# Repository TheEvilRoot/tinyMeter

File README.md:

# tinyMeter

Current/voltage meter board for:
- USB-C passthrough with PD support
- USB-C - USB-A 5V rail 
- DC-Jack passthrough

ESP32-S3 MCU is powered from separate master USB-C port with USB communication enabled. MCU is communicating with INA3221 IC via I2C. Separate I2C lines are connected to SSD1306 display connector (GND, 3V3, SCL, SDA). MCU also connected to 5 user buttons for user interaction and 3 LEDs.

## PCB

Board is implemented as 4-layer PCB with [Signal/GND - GND - 3V3 - Signal/GND] stackup (theoretically can be shrinked to 2 layers).

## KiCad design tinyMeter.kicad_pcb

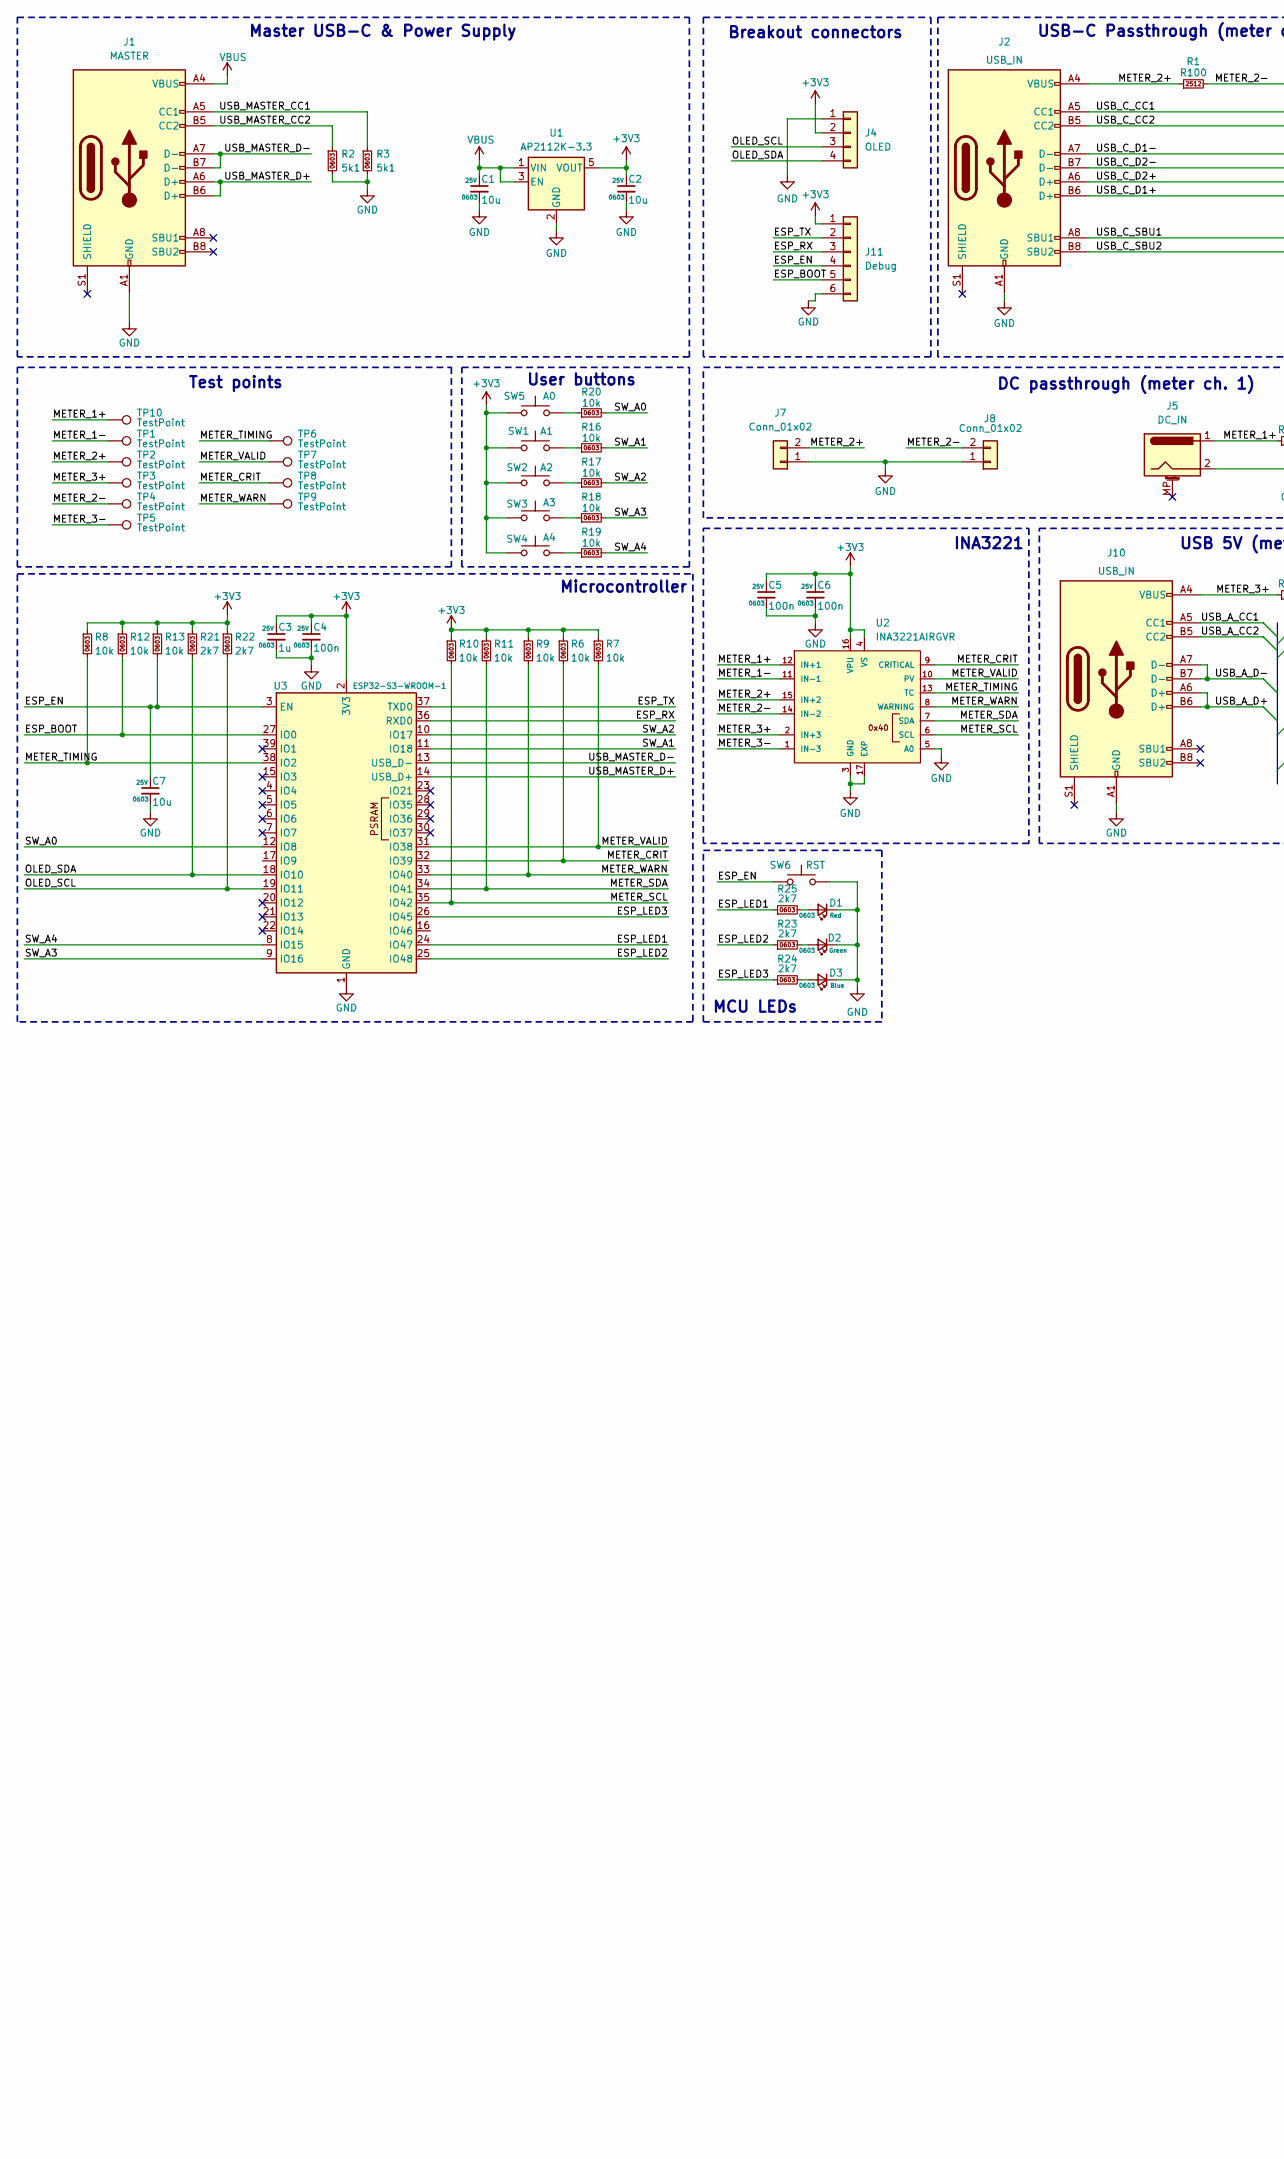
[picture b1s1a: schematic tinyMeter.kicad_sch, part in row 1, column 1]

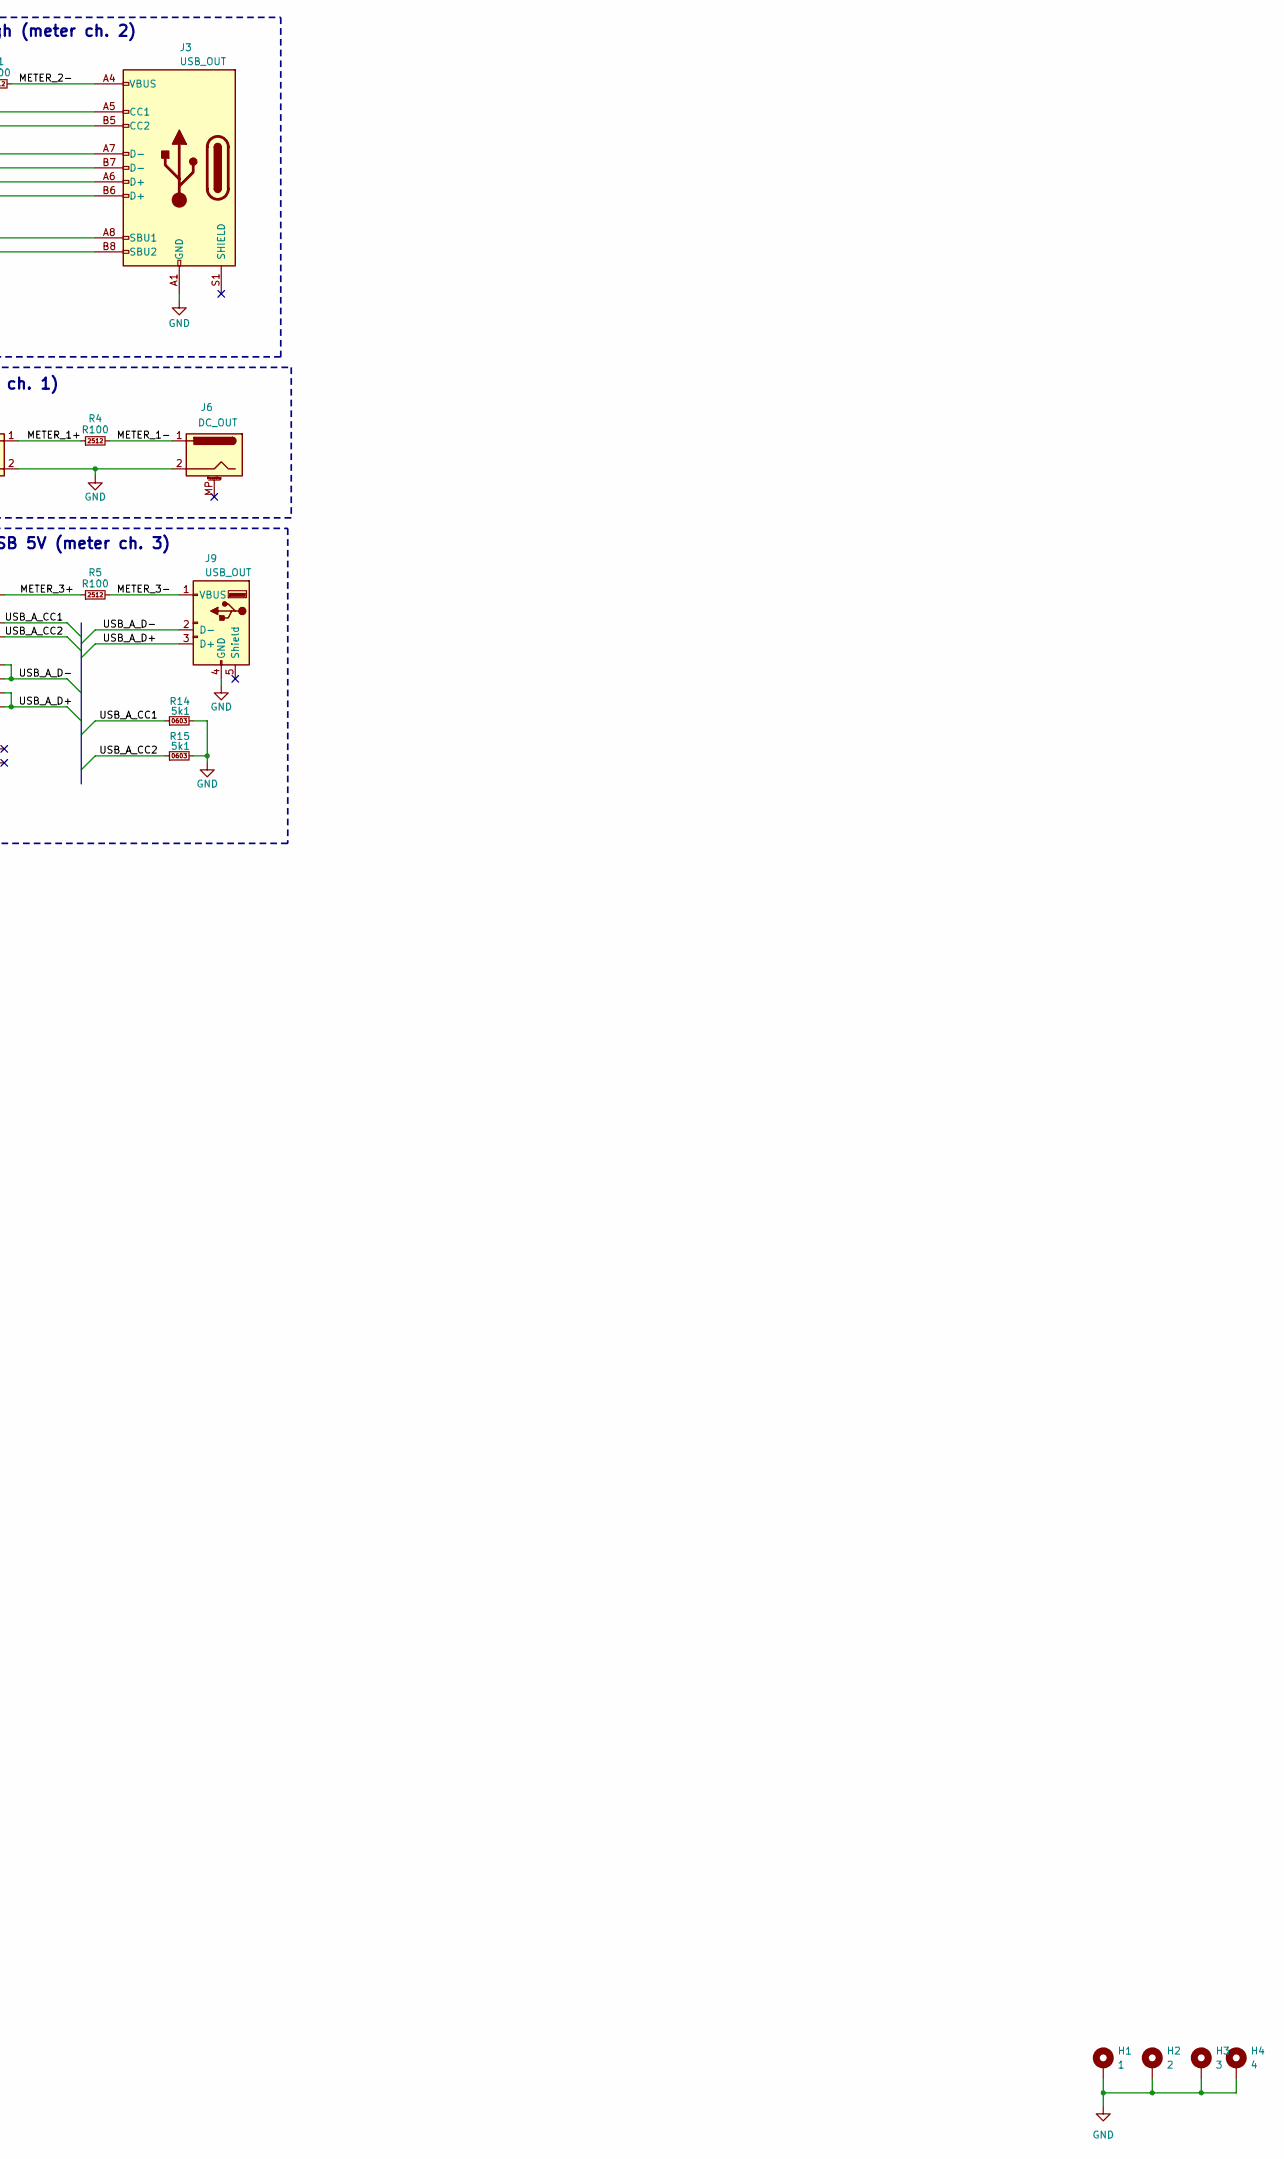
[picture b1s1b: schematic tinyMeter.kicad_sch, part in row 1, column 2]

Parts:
C1, C2, C7: 10u; C_0603_1608Metric; Rating 25V
C3: 1u; C_0603_1608Metric; Rating 25V
C4, C5, C6: 100n; C_0603_1608Metric; Rating 25V
D1: Red; LED_0603_1608Metric
D2: Green; LED_0603_1608Metric
D3: Blue; LED_0603_1608Metric
H1: 1; MountingHole_2.7mm_M2.5_DIN965_Pad
H2: 2; MountingHole_2.7mm_M2.5_DIN965_Pad
H3: 3; MountingHole_2.7mm_M2.5_DIN965_Pad
H4: 4; MountingHole_2.7mm_M2.5_DIN965_Pad
J1: MASTER; USB_C_Receptacle_HRO_TYPE-C-31-M-12
J2, J10: USB_IN; USB_C_Receptacle_HRO_TYPE-C-31-M-12
J3: USB_OUT; USB_C_Receptacle_HRO_TYPE-C-31-M-12
J4: OLED; PinSocket_1x04_P2.54mm_Vertical
J5: DC_IN; BarrelJack_Horizontal
J6: DC_OUT; BarrelJack_Horizontal
J7, J8: Conn_01x02; PinHeader_1x02_P2.54mm_Vertical
J9: USB_OUT; TE_292303-1
J11: Debug; PinHeader_1x06_P1.27mm_Vertical
R1, R4, R5: R100; R_2512_6332Metric
R2, R3, R14, R15: 5k1; R_0603_1608Metric
R6, R7, R8, R9, R10, R11, R12, R13, R16, R17, R18, R19, R20: 10k; R_0603_1608Metric
R21, R22, R23, R24, R25: 2k7; R_0603_1608Metric
SW1: A1; KLS7-TS3401
SW2: A2; KLS7-TS3401
SW3: A3; KLS7-TS3401
SW4: A4; KLS7-TS3401
SW5: A0; KLS7-TS3401
SW6: RST; KLS7-TS3401
TP1, TP2, TP3, TP4, TP5, TP6, TP7, TP8, TP9, TP10: TestPoint; TestPoint_Pad_D1.0mm
U1: AP2112K-3.3; SOT-23-5
U2: INA3221AIRGVR; QFN65P400X400X100-17N
U3: ESP32-S3-WROOM-1

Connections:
+3V3: C2.1, C3.1, C4.1, C5.1, C6.1, J4.2, J11.1, R6.1, R7.1, R8.1, R9.1, R10.1, R11.1, R12.1, R13.1, R21.1, R22.1, SW1.1, SW2.1, SW3.1, SW4.1, SW5.1, U1.5 (VOUT), U2.4 (VS), U2.16 (VPU), U3.2 (3V3)
/ESP_BOOT: J11.5, R12.2, U3.27 (IO0)
/ESP_EN: C7.1, J11.4, R13.2, SW6.1, U3.3 (EN)
/ESP_LED1: R25.1, U3.24 (IO47)
/ESP_LED2: R23.1, U3.25 (IO48)
/ESP_LED3: R24.1, U3.26 (IO45)
/ESP_RX: J11.3, U3.36 (RXD0)
/ESP_TX: J11.2, U3.37 (TXD0)
/METER_1+: J5.1, R4.1, TP10.1, U2.12 (IN+1)
/METER_1-: J6.1, R4.2, TP1.1, U2.11 (IN-1)
/METER_2+: J2.A4 (VBUS), J2.A9 (VBUS), J2.B4 (VBUS), J2.B9 (VBUS), J7.2, R1.1, TP2.1, U2.15 (IN+2)
/METER_2-: J3.A4 (VBUS), J3.A9 (VBUS), J3.B4 (VBUS), J3.B9 (VBUS), J8.2, R1.2, TP4.1, U2.14 (IN-2)
/METER_3+: J10.A4 (VBUS), J10.A9 (VBUS), J10.B4 (VBUS), J10.B9 (VBUS), R5.1, TP3.1, U2.2 (IN+3)
/METER_3-: J9.1 (VBUS), R5.2, TP5.1, U2.1 (IN-3)
/METER_CRIT: R6.2, TP8.1, U2.9 (CRITICAL), U3.32 (IO39)
/METER_SCL: R10.2, U2.6 (SCL), U3.35 (IO42)
/METER_SDA: R11.2, U2.7 (SDA), U3.34 (IO41)
/METER_TIMING: R8.2, TP6.1, U2.13 (TC), U3.38 (IO2)
/METER_VALID: R7.2, TP7.1, U2.10 (PV), U3.31 (IO38)
/METER_WARN: R9.2, TP9.1, U2.8 (WARNING), U3.33 (IO40)
/OLED_SCL: J4.3, R22.2, U3.19 (IO11)
/OLED_SDA: J4.4, R21.2, U3.18 (IO10)
/SW_A0: R20.2, U3.12 (IO8)
/SW_A1: R16.2, U3.11 (IO18)
/SW_A2: R17.2, U3.10 (IO17)
/SW_A3: R18.2, U3.9 (IO16)
/SW_A4: R19.2, U3.8 (IO15)
/USB_A_CC1: J10.A5 (CC1), R14.1
/USB_A_CC2: J10.B5 (CC2), R15.1
/USB_A_D+: J9.3 (D+), J10.A6 (D+), J10.B6 (D+)
/USB_A_D-: J9.2 (D-), J10.A7 (D-), J10.B7 (D-)
/USB_C_CC1: J2.A5 (CC1), J3.A5 (CC1)
/USB_C_CC2: J2.B5 (CC2), J3.B5 (CC2)
/USB_C_D1+: J2.B6 (D+), J3.B6 (D+)
/USB_C_D1-: J2.A7 (D-), J3.A7 (D-)
/USB_C_D2+: J2.A6 (D+), J3.A6 (D+)
/USB_C_D2-: J2.B7 (D-), J3.B7 (D-)
/USB_C_SBU1: J2.A8 (SBU1), J3.A8 (SBU1)
/USB_C_SBU2: J2.B8 (SBU2), J3.B8 (SBU2)
/USB_MASTER_CC1: J1.A5 (CC1), R3.1
/USB_MASTER_CC2: J1.B5 (CC2), R2.1
/USB_MASTER_D+: J1.A6 (D+), J1.B6 (D+), U3.14 (USB_D+)
/USB_MASTER_D-: J1.A7 (D-), J1.B7 (D-), U3.13 (USB_D-)
GND: C1.2, C2.2, C3.2, C4.2, C5.2, C6.2, C7.2, D1.1 (K), D2.1 (K), D3.1 (K), H1.1, H2.1, H3.1, H4.1, J1.A1 (GND), J1.A12 (GND), J1.B1 (GND), J1.B12 (GND), J2.A1 (GND), J2.A12 (GND), J2.B1 (GND), J2.B12 (GND), J3.A1 (GND), J3.A12 (GND), J3.B1 (GND), J3.B12 (GND), J4.1, J5.2, J6.2, J7.1, J8.1, J9.4 (GND), J10.A1 (GND), J10.A12 (GND), J10.B1 (GND), J10.B12 (GND), J11.6, R2.2, R3.2, R14.2, R15.2, SW6.2, U1.2 (GND), U2.3 (GND), U2.5 (A0), U2.17 (EXP), U3.1 (GND), U3.40 (GND), U3.41 (GND)
unnamed: D1.2 (A), R25.2
unnamed: D2.2 (A), R23.2
unnamed: D3.2 (A), R24.2
unnamed: R16.1, SW1.2
unnamed: R17.1, SW2.2
unnamed: R18.1, SW3.2
unnamed: R19.1, SW4.2
unnamed: R20.1, SW5.2
VBUS: C1.1, J1.A4 (VBUS), J1.A9 (VBUS), J1.B4 (VBUS), J1.B9 (VBUS), U1.1 (VIN), U1.3 (EN)

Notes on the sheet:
USB 5V (meter ch. 3)
INA3221
DC passthrough (meter ch. 1)
Master USB-C & Power Supply
Microcontroller
MCU LEDs
User buttons
USB-C Passthrough (meter ch. 2)
Breakout connectors
Test points

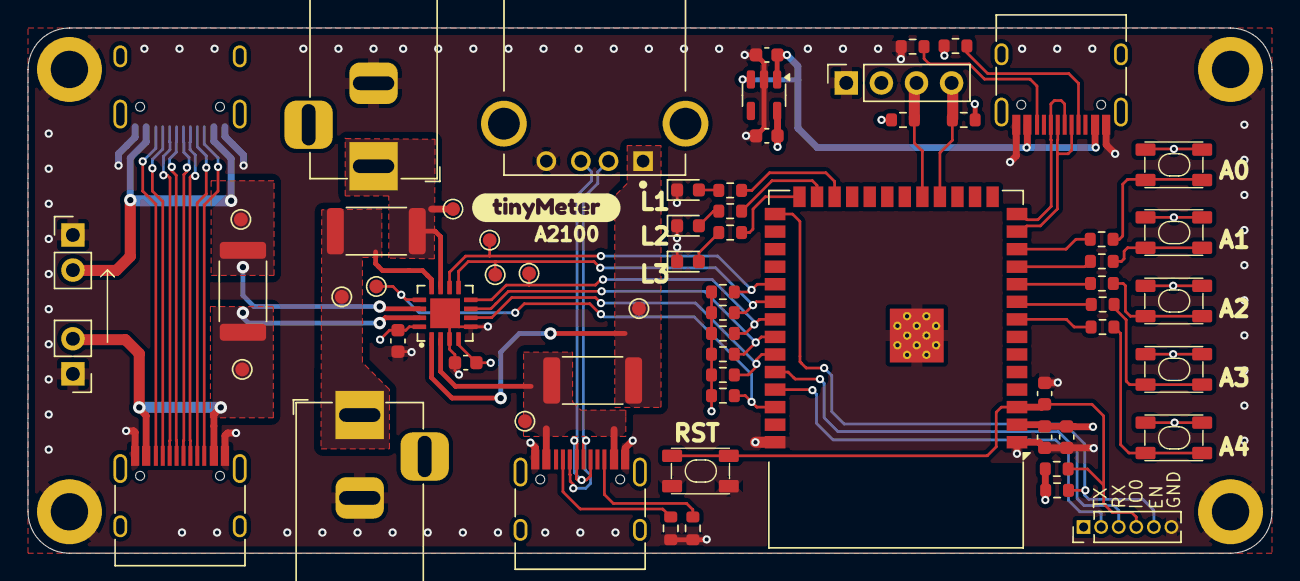
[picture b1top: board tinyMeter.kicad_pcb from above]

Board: 4 copper layers, 90.0 x 38.0 mm, 70 parts (1 on the bottom side), 53 nets.

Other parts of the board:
kibuzzard-68053040: G***; kibuzzard-68053040

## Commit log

2025-01-17 v1 start
2025-01-17 Rough schematic and start of layout
2025-01-18 Rough layout and routing
2025-01-18 More layout
    - Some traces refactor
    - Add debug connector with UART lines
    - Add external WiFi/BT connector and selector for PCB/Ext
    - Add WS8212B LED just for fun
    - Add power indication LED on 3V3
    - Remove RefDes silkscreen; add useful silkscreen
2025-01-19 Fixes and schematic refactor
    - Refactor schematic to get more space
    - Assign nets where missing
    - Change footprint of USB-C
    - Add 3D model for USB-C footprint
    - Changes to board setup
2025-01-19 Some rerouting. Via stitching. Align mouting holes
2025-01-22 Fix display connector orientation
2025-01-22 Remove most of knockouts from silkscreen
2025-01-22 Tiny rerouting
2025-02-01 Fix DC voltage rating
2025-04-09 Working on v2
2025-04-17 Version 2 finish
2025-04-17 v2 readme
2025-04-27 Working
